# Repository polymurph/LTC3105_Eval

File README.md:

#LTC3105_EVAL

## Active Versions

### V1.X.X

[V1.X.X](https://github.com/polymurph/LTC3105_Eval/tree/V1)

[Latest release](https://github.com/polymurph/LTC3105_Eval/releases/tag/V1_0_0_0_2024_12_30)

### V0.X.X

[V0.X.X](https://github.com/polymurph/LTC3105_Eval/tree/V0)

© Edwin Koch 2024, This work is licenced under [CERN-OHL-P V 2.0](https://ohwr.org/cern_ohl_p_v2.txt).

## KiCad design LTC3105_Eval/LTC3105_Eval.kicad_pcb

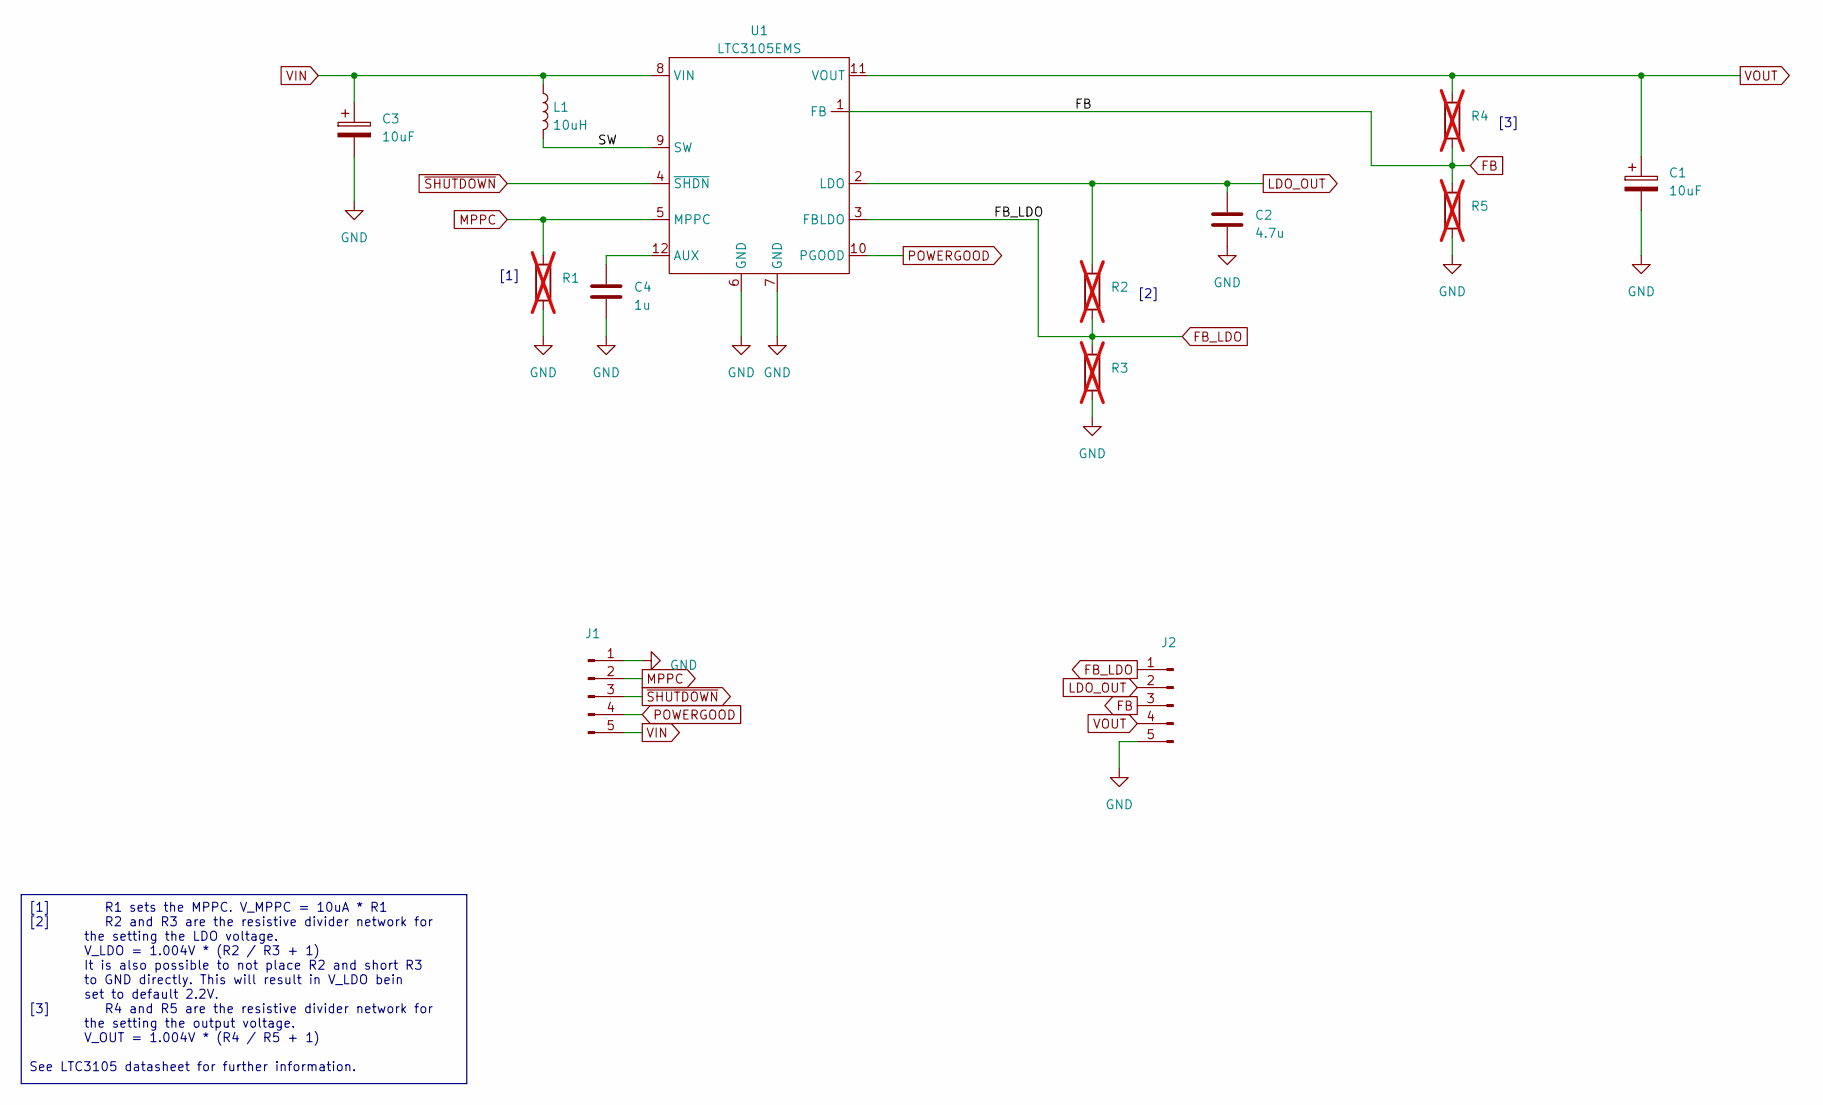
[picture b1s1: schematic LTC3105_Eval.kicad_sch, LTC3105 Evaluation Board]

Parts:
C1, C3: 10uF; CP_EIA-3216-18_Kemet-A_Pad1.58x1.35mm_HandSolder
C2: 4.7u; C_1206_3216Metric
C4: 1u; C_1206_3216Metric
J1, J2: Conn_01x05_Pin; PinHeader_1x05_P2.54mm_Vertical
L1: 10uH; L_Coilcraft_MSS5131-XXX_handsolder
R1, R2, R3, R4, R5: R_0603_1608Metric_Pad0.98x0.95mm_HandSolder; not fitted
U1: LTC3105EMS; MSOP-12_3x4mm_P0.65mm

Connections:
/SW: L1.2, U1.9 (SW)
FB: J2.3, R4.2, R5.1, U1.1 (FB)
FB_LDO: J2.1, R2.2, R3.1, U1.3 (FBLDO)
GND: C1.2, C2.2, C3.2, C4.2, J1.1, J2.5, R1.2, R3.2, R5.2, U1.6 (GND), U1.7 (GND)
LDO_OUT: C2.1, J2.2, R2.1, U1.2 (LDO)
MPPC: J1.2, R1.1, U1.5 (MPPC)
unnamed: C4.1, U1.12 (AUX)
POWERGOOD: J1.4, U1.10 (PGOOD)
VIN: C3.1, J1.5, L1.1, U1.8 (VIN)
VOUT: C1.1, J2.4, R4.1, U1.11 (VOUT)
~SHUTDOWN: J1.3, U1.4 (~SHDN)

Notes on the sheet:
[1] R1 sets the MPPC. V_MPPC = 10uA * R1 [2] R2 and R3 are the resistive divider network for the setting the LDO voltage. V_LDO = 1.004V * (R2 / R3 + 1) It is also possible to not place R2 and short R3 to GND directly. This will result in V_LDO bein set to default 2.2V. [3] R4 and R5 are the resist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
[1]
[2]
[3]

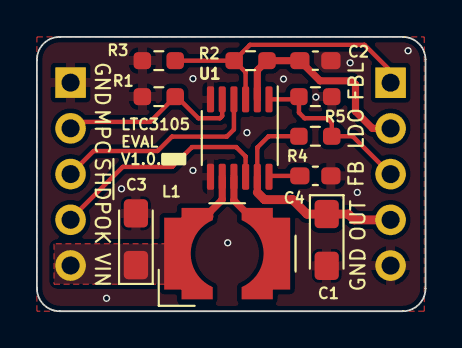
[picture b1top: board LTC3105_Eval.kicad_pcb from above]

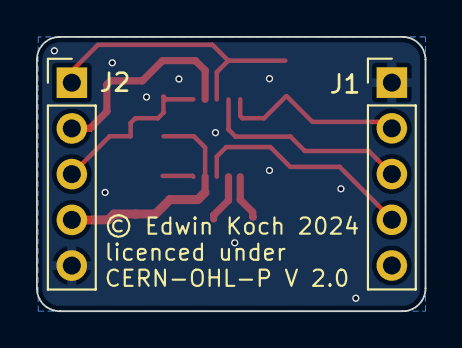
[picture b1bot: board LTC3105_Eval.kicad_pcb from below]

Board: 2 copper layers, 21.6 x 15.2 mm, 13 parts (2 on the bottom side), 11 nets.

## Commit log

2024-04-03 added readme
2024-04-03 added empty kicad Project
2024-04-06 work on circuit + layout
2024-04-13 first draft of layout and schematic
2024-06-21 Create LICENCE. Closed #2
2024-06-21 small changes to layout
2024-06-21 added QR code to PCB with the v0 repo branch url
2024-06-21 work on QR code
2024-06-22 work on DRC
2024-09-01 release V0_0_0_0_2024_09_01
2024-12-30 work on issues
2024-12-30 finished V1
2024-12-30 removed problematic file
2024-12-30 replaced file
2024-12-30 resolved #8, #7, #6 and #5 ; closed #5 and #3
